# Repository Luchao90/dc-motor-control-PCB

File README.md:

# DC MOTOR CONTROL

This work is realize in context of "pcb design" course from embedded system career FIUBA 2020, for [NOVOTEC](https://www.novotecargentina.com/ofertas.php) company.

# Be careful - NOT TESTED YET.

## SPECS

* Input: 8-30V @30A depends on motor or LOAD.
* PWM Frequency: 30KHz max.
*: 1 DC motor bi directional or 2 DC motor uni directional.
* Alternative: Any kind of PWM control like lamp dimmer for example.
* Control interface: I2C, PWM and ADC.

## Schematic 

[Schematic](pcb/prints/dc_motor.pdf)

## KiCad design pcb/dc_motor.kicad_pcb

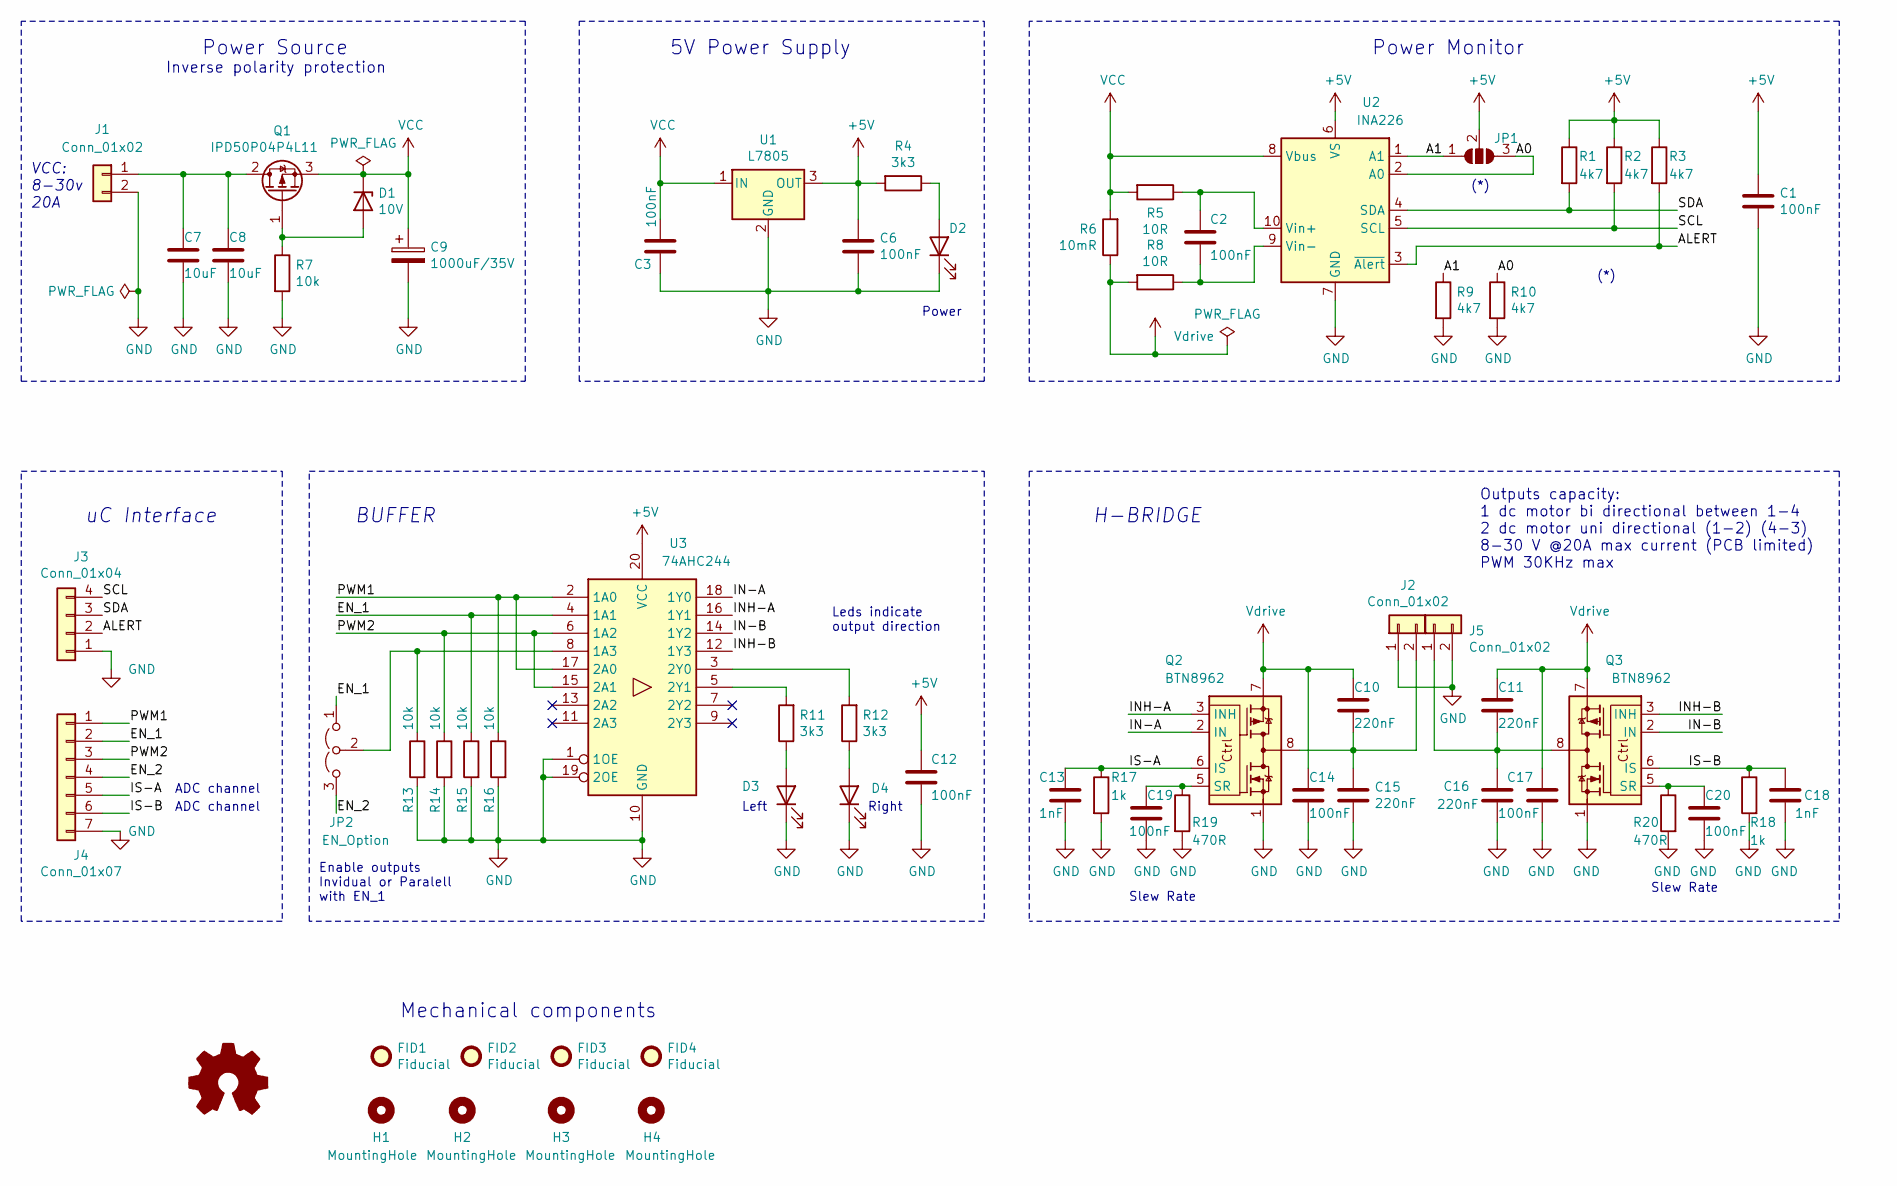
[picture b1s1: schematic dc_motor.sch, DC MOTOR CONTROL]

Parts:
C1, C2, C3, C6, C12, C14, C17, C19, C20: 100nF; C_0603_1608Metric; digikey# 1276-CL10B104KB8WPNDCT-ND
C7, C8: 10uF; C_0805_2012Metric; digikey# 490-10505-1-ND
C9: 1000uF/35V; CP_Radial_D10.0mm_P5.00mm; digikey# 1189-3736-1-ND
C10, C11, C15, C16: 220nF; C_0603_1608Metric; digikey# 311-1830-1-ND
C13, C18: 1nF; C_0603_1608Metric; digikey# 399-7842-1-ND
D1: 10V; D_SOD-123; digikey# BZT52C10-FDICT-ND
D2, D3, D4: Red led 0603; LED_0603_1608Metric; digikey# 732-4978-1-ND
FID1, FID2, FID3, FID4: Fiducial; Fiducial_0.5mm_Mask1.5mm; digikey# dnp
H1, H2, H3, H4: MountingHole; MountingHole_3.2mm_M3_ISO14580; digikey# dnp
J1, J2, J5: Conn_01x02; PhoenixContact_MCV_1,5_2-G-5.08_1x02_P5.08mm_Vertical; digikey# 732-2052-ND
J3: Conn_01x04; Molex_KK-254_AE-6410-04A_1x04_P2.54mm_Vertical; digikey# WM4202-ND
J4: Conn_01x07; Molex_KK-254_AE-6410-07A_1x07_P2.54mm_Vertical; digikey# WM4305-ND
JP1: SolderJumper_3_Open; SolderJumper-3_P1.3mm_Open_RoundedPad1.0x1.5mm; digikey# dnp
JP2: EN_Option; PinHeader_1x03_P2.54mm_Vertical; digikey# 732-5316-ND
LOGO1: Logo_Open_Hardware_Small; OSHW-Logo2_9.8x8mm_SilkScreen; digikey# dnp
Q1: IPD50P04P4L11; TO-252-2; digikey# 448-IPD50P04P4L11ATMA2CT-ND
Q2, Q3: BTN8962; TO-263-7_TabPin8; digikey# BTN8962TAAUMA1
R1, R2, R3, R9, R10: 4k7; R_0603_1608Metric; digikey# 311-4.7KGRCT-ND
R4, R11, R12: 3k3; R_0603_1608Metric; digikey# 311-3.3KGRCT-ND
R5, R8: 10R; R_0603_1608Metric; digikey# 311-10.0HRCT-ND
R6: 10mR; R_2512_6332Metric; digikey# CRA2512-FZ-R010ELFCT-ND
R7, R13, R14, R15, R16: 10k; R_0603_1608Metric; digikey# 311-10.0KHRCT-ND
R17, R18: 1k; R_0603_1608Metric; digikey# 311-1.00KHRCT-ND
R19, R20: 470R; R_0603_1608Metric; digikey# 311-470HRCT-ND
U1: L7805; TO-252-3_TabPin2; digikey# 497-1170-1-ND
U2: INA226; VSSOP-10_3x3mm_P0.5mm; digikey# 296-29034-1-ND
U3: 74AHC244; TSSOP-20_4.4x6.5mm_P0.65mm; digikey# 296-SN74AHC244QPWRQ1CT-ND

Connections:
+5V: C1.1, C6.1, C12.1, JP1.2 (C), R1.1, R2.1, R3.1, R4.2, U1.3 (OUT), U2.6 (VS), U3.20 (VCC)
/A0: JP1.3 (B), R10.1, U2.2 (A0)
/A1: JP1.1 (A), R9.1, U2.1 (A1)
/ALERT: J3.2, R3.2, U2.3 (~Alert~)
/EN_1: J4.2, JP2.1 (A), R15.1, U3.4 (1A1)
/EN_2: J4.4, JP2.3 (B)
/IN-A: Q2.2 (IN), U3.18 (1Y0)
/IN-B: Q3.2 (IN), U3.14 (1Y2)
/INH-A: Q2.3 (INH), U3.16 (1Y1)
/INH-B: Q3.3 (INH), U3.12 (1Y3)
/IS-A: C13.1, J4.5, Q2.6 (IS), R17.1
/IS-B: C18.1, J4.6, Q3.6 (IS), R18.1
/PWM1: J4.1, R16.1, U3.2 (1A0), U3.17 (2A0)
/PWM2: J4.3, R14.1, U3.6 (1A2), U3.15 (2A1)
/SCL: J3.4, R2.2, U2.5 (SCL)
/SDA: J3.3, R1.2, U2.4 (SDA)
GND: C1.2, C3.2, C6.2, C7.2, C8.2, C9.2, C12.2, C13.2, C14.2, C15.2, C16.2, C17.2, C18.2, C19.2, C20.2, D2.1 (K), D3.1 (K), D4.1 (K), J1.2, J2.1, J3.1, J4.7, J5.2, Q2.1, Q3.1, R7.2, R9.2, R10.2, R13.2, R14.2, R15.2, R16.2, R17.2, R18.2, R19.2, R20.2, U1.2 (GND), U2.7 (GND), U3.1 (1OE), U3.10 (GND), U3.19 (2OE)
unnamed: C2.1, R5.1, U2.10 (Vin+)
unnamed: C2.2, R8.1, U2.9 (Vin-)
unnamed: C7.1, C8.1, J1.1, Q1.2 (D)
unnamed: C10.2, C15.1, J2.2, Q2.4, Q2.8
unnamed: C11.2, C16.1, J5.1, Q3.4, Q3.8
unnamed: C19.1, Q2.5 (SR), R19.1
unnamed: C20.1, Q3.5 (SR), R20.1
unnamed: D1.2 (A), Q1.1 (G), R7.1
unnamed: D2.2 (A), R4.1
unnamed: D3.2 (A), R11.1
unnamed: D4.2 (A), R12.1
unnamed: JP2.2 (C), R13.1, U3.8 (1A3)
unnamed: R11.2, U3.5 (2Y1)
unnamed: R12.2, U3.3 (2Y0)
VCC: C3.1, C9.1, D1.1 (K), Q1.3 (S), R5.2, R6.2, U1.1 (IN), U2.8 (Vbus)
Vdrive: C10.1, C11.1, C14.1, C17.1, Q2.7, Q3.7, R6.1, R8.2

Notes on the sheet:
H-BRIDGE
Inverse polarity protection
Power Source
Power Monitor
(*)
5V Power Supply
BUFFER
Mechanical components
Outputs capacity: 1 dc motor bi directional between 1-4 2 dc motor uni directional (1-2) (4-3) 8-30 V @20A max current (PCB limited) PWM 30KHz max
ADC channel
uC Interface
VCC: 8-30v 20A
Leds indicate output direction
Slew Rate
Enable outputs Invidual or Paralell with EN_1
Power
Left
Right

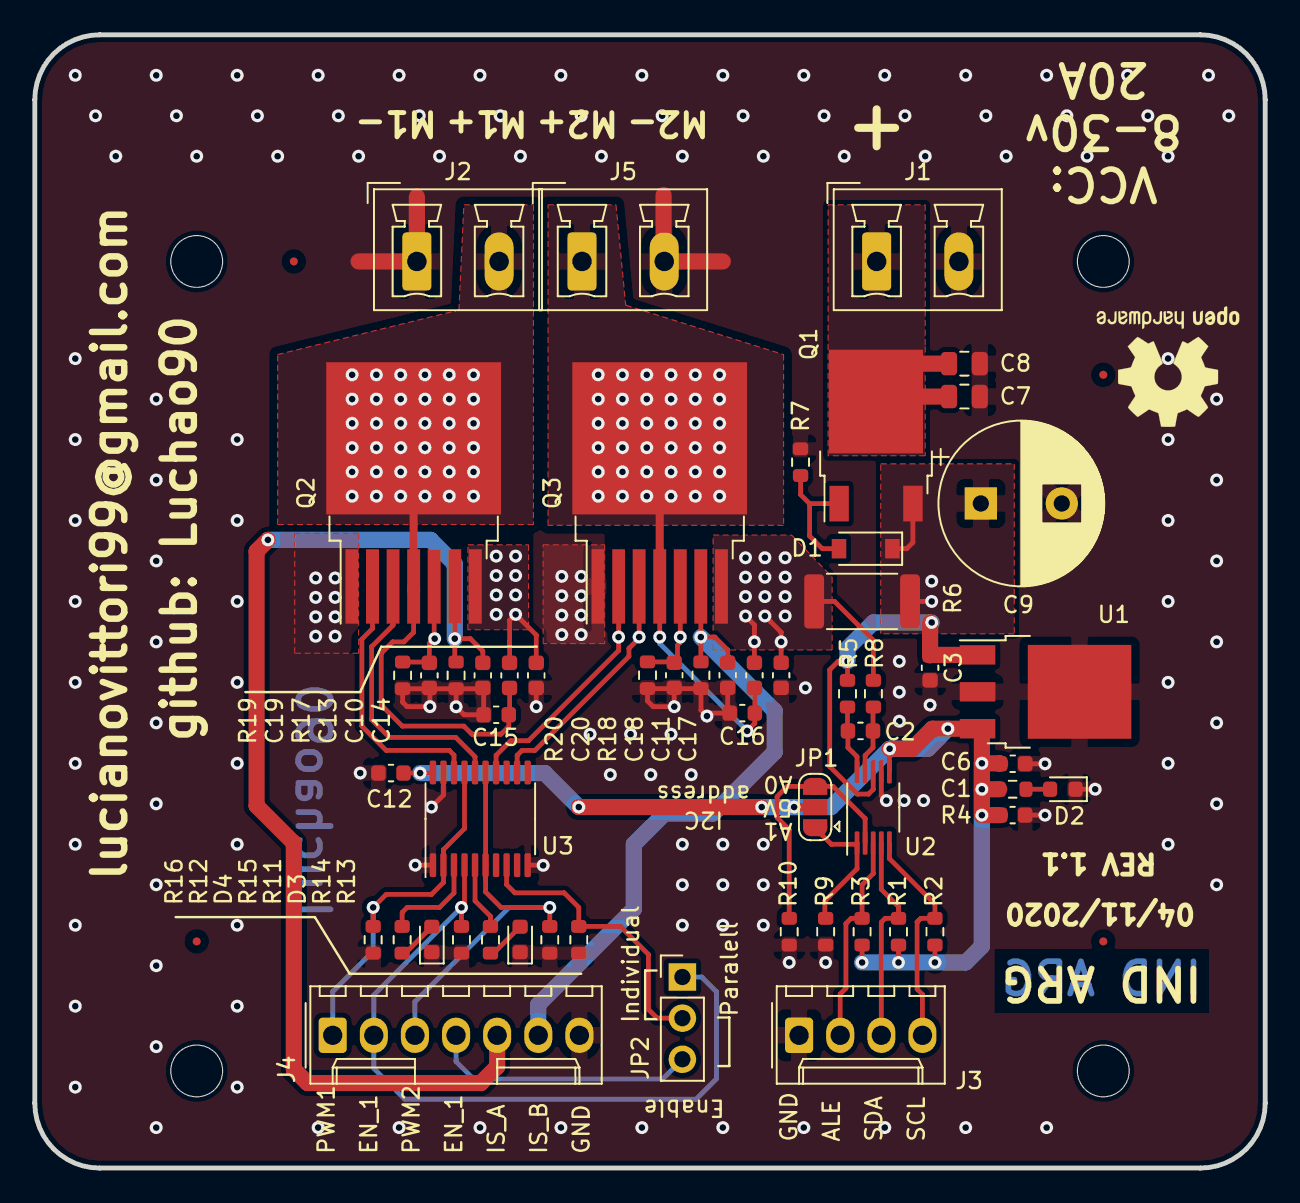
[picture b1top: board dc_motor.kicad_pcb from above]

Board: 2 copper layers, 76.0 x 70.0 mm, 64 parts (0 on the bottom side), 33 nets.

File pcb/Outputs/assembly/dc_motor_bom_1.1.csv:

Reference, Quantity, Value, Footprint, digikey#, manf#
C1 C2 C3 C6 C12 C14 C17 C19 C20 ,9,100nF,Capacitor_SMD:C_0603_1608Metric,1276-CL10B104KB8WPNDCT-ND,CL10B104KB8WPND
C10 C11 C15 C16 ,4,220nF,Capacitor_SMD:C_0603_1608Metric,311-1830-1-ND,CC0603ZRY5V9BB224
C13 C18 ,2,1nF,Capacitor_SMD:C_0603_1608Metric,399-7842-1-ND,C0603C103M5RACTU
C7 C8 ,2,10uF,Capacitor_SMD:C_0805_2012Metric,490-10505-1-ND,GRM21BC8YA106ME11L
C9 ,1,1000uF/35V,Capacitor_THT:CP_Radial_D10.0mm_P5.00mm,1189-3736-1-ND,35PK1000MEFCT810X20
D1 ,1,10V,Diode_SMD:D_SOD-123,BZT52C10-FDICT-ND,BZT52C10-7-F
D2 D3 D4 ,3,Red led 0603,LED_SMD:LED_0603_1608Metric,732-4978-1-ND,150060RS75000
J1 J2 J5 ,3,Conn_01x02,"Connector_Phoenix_MC_HighVoltage:PhoenixContact_MCV_1,5_2-G-5.08_1x02_P5.08mm_Vertical",732-2052-ND,691311500002
J3 ,1,Conn_01x04,Connector_Molex:Molex_KK-254_AE-6410-04A_1x04_P2.54mm_Vertical,WM4202-ND,22232041
J4 ,1,Conn_01x07,Connector_Molex:Molex_KK-254_AE-6410-07A_1x07_P2.54mm_Vertical,WM4305-ND,22053071
JP2 ,1,EN_Option,Connector_PinHeader_2.54mm:PinHeader_1x03_P2.54mm_Vertical,732-5316-ND,61300311121
Q1 ,1,IPD50P04P4L11,Package_TO_SOT_SMD:TO-252-2,448-IPD50P04P4L11ATMA2CT-ND,IPD50P04P4L11ATMA2
Q2 Q3 ,2,BTN8962,Package_TO_SOT_SMD:TO-263-7_TabPin8,BTN8962TAAUMA1,BTN8962TAAUMA1INCT-ND
R1 R2 R3 R9 R10 ,5,4k7,Resistor_SMD:R_0603_1608Metric,311-4.7KGRCT-ND,RC0603JR-074K7L
R17 R18 ,2,1k,Resistor_SMD:R_0603_1608Metric,311-1.00KHRCT-ND,RC0603FR-071KL
R19 R20 ,2,470R,Resistor_SMD:R_0603_1608Metric,311-470HRCT-ND,RC0603FR-07470RL
R4 R11 R12 ,3,3k3,Resistor_SMD:R_0603_1608Metric,311-3.3KGRCT-ND,RC0603JR-073K3L
R6 ,1,10mR,Resistor_SMD:R_2512_6332Metric,CRA2512-FZ-R010ELFCT-ND,CRA2512-FZ-R010ELF
R7 R13 R14 R15 R16 ,5,10k,Resistor_SMD:R_0603_1608Metric,311-10.0KHRCT-ND,RC0603FR-0710KL
R5 R8 ,2,10R,Resistor_SMD:R_0603_1608Metric,311-10.0HRCT-ND,RC0603FR-0710RL
U1 ,1,L7805,Package_TO_SOT_SMD:TO-252-3_TabPin2,497-1170-1-ND,L7805ABD2T-TR
U2 ,1,INA226,Package_SO:VSSOP-10_3x3mm_P0.5mm,296-29034-1-ND,INA226AIDGSR
U3 ,1,74AHC244,Package_SO:TSSOP-20_4.4x6.5mm_P0.65mm,296-SN74AHC244QPWRQ1CT-ND,SN74AHC244QPWRQ1

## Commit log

2020-09-18 init
2020-09-18 project folder
2020-09-19 schematics without values and footprint yet
2020-09-20 sch values
2020-09-21 footprints
2020-10-08 git ignore
2020-10-09 Sch complete.
    first revision.
2020-10-16 Part number changes
2020-10-16 Rev1
    Correcciones de primera revisión del profesor, hasta el esquemático.
2020-10-31 Placement
2020-11-01 3dshapes
2020-11-01 board dimension
    change 1 capacitor value.
2020-11-01 routing 01
2020-11-01 pcb 01
2020-11-02 fix unconnected
2020-11-04 Diego reviews 1
2020-11-04 add open hardware logo
2020-11-04 cleaning
2020-11-04 add outputs fab
2020-11-04 readme info
2020-11-04 schematic print
2020-11-04 update image
2020-11-05 interactive component place
2020-11-05 change gitignore for BOM
2020-11-05 symbols field
2020-11-05 add BOM
2020-11-05 prints place
2020-11-05 zip folder exclude
2020-11-14 change #digikey to digikey#
2020-11-14 csv BOM
2020-11-14 kibom update
2020-11-15 economic BOM
2020-11-15 Rev 1.1
    Change power connectors and limited current to 20A

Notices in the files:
pcb/dc_motor.kicad_pcb:
CERN Open Hardware Licence Version 2 - Permissive
